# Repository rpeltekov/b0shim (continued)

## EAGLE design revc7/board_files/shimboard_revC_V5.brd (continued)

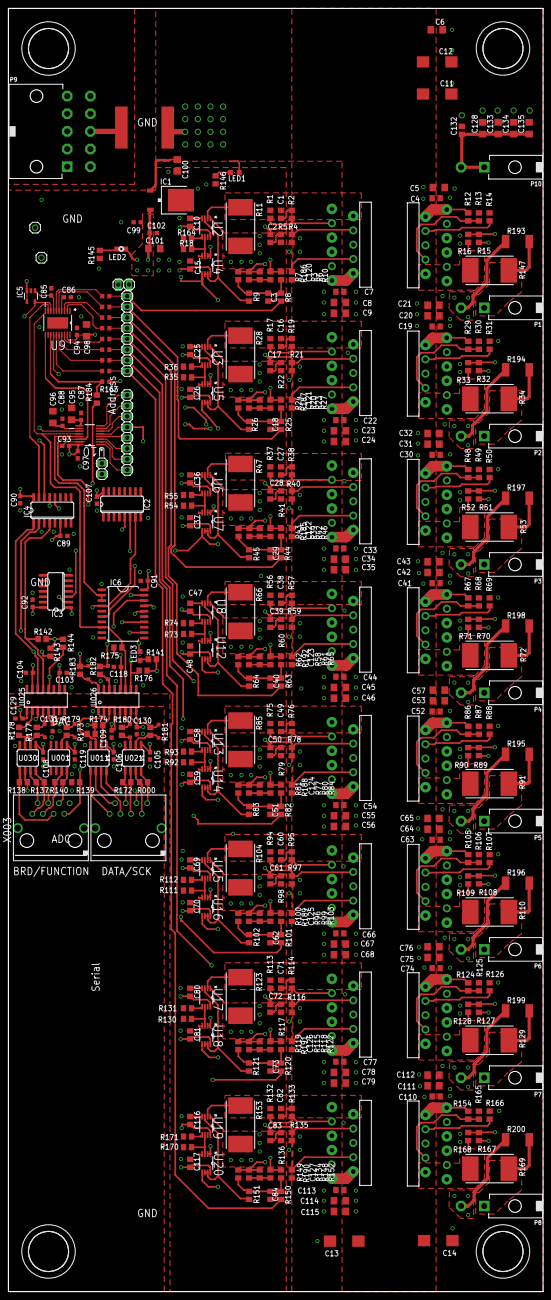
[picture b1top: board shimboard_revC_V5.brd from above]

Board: 4 copper layers, 127.0 x 304.8 mm, 411 parts (0 on the bottom side), 229 nets.

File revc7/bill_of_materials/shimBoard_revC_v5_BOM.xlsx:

Qty | Value | Device | Package | Manufacturer Part # | Parts | Description | MPN | SPICEPREFIX
SMT Components
3 |  | LEDCHIPLED_0805 | CHIPLED_0805 | LTST-C191KRKT | LED1, LED2, LED3 | LED
8 | 0 | R-US_R0603 | R0603 | ‎ERJ-3GEY0R00V‎ | R155, R156, R157, R158, R159, R160, R161, R162 | RESISTOR, | American symbol | R
24 | 0.1uF | C-USC0603 | C0603 | CC0603ZRY5V9BB104‎ | C85, C86, C87, C88, C89, C90, C91, C92, C93, C94, C99, C102, C103, C104, C105, 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 | CAPACITOR | American symbol | C
33 | 0.1uF | C-USC0805 | C0805 | CL21F104ZBCNNNC‎ | C4, C7, C10, C15, C19, C22, C25, C26, C30, C33, C36, C37, C41, C44, C47, C48, C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 | CAPACITOR | American symbol | C
16 | 0.2 | R-US_R4527 | R4527 | WSR5R2000FEA | R11, R28, R34, R47, R53, R66, R72, R85, R91, R104, R110, R123, R129, R147, R153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 | RESISTOR | American symbol | R
1 | 881070 | 881070 | 881 | ‎0881070.UR‎ | U031
7 | 100 | R-US_R0805 | R0805 | ‎ERA-6AEB101V‎ | R000, R137, R138, R139, R140, R172, R184 | RESISTOR | American symbol | 100
16 | 100pF | C-USC0805 | C0805 | 08051A101FAT2A‎ | C1, C2, C16, C17, C27, C28, C38, C39, C49, C50, C60, C61, C71, C72, C82, C83 | CAPACITOR | American symbol | C
4 | 100u | CPOL-USD/7343-31W | D/7343-31W | T491X107K025AT‎ | C11, C12, C13, C14 | POLARIZED CAPACITOR | American symbol | C
1 | 10k | R-US_R0603 | R0603 | RNCF0805DTE10K0‎ | R163 | RESISTOR | American symbol | R
48 | 10k | R-US_R0805 | R0805 | RNCF0805DTE10K0‎ | R8, R9, R10, R14, R18, R25, R26, R27, R31, R35, R36, R44, R45, R46, R50, R54, R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 | RESISTOR | American symbol | R
41 | 10uF | C-USC1206 | C1206 | CL31A106KAHNNNE‎ | C5, C6, C8, C9, C20, C21, C23, C24, C31, C32, C34, C35, C42, C43, C45, C46, C53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 | CAPACITOR | American symbol | C
7 | 1N4148 | 1N4148 | 1N4148 | 1N4148W-7-F | U040, U041, U042, U043, U044, U045, U046
1 | 1n | C-USC0805 | C0805 | C0805C102K1RACTU‎ | C3 | CAPACITOR | American symbol | 1n
7 | 1n | C-USC0805 | C0805 | C0805C102K1RACTU‎ | C18, C29, C40, C51, C62, C73, C84 | CAPACITOR | American symbol | C
1 | 1uF | C-USC0603 | C0603 | CL10A105KA8NNNC‎ | C97 | CAPACITOR | American symbol | C
8 | 220p | C-USC0805 | C0805 | C0805C221M5RACTU‎ | C120, C121, C122, C123, C124, C125, C126, C127 | CAPACITOR | American symbol | C
8 | 22k | R-US_R0805 | R0805 | KTR10EZPF2202‎ | R3, R20, R39, R58, R77, R96, R115, R134 | RESISTOR | American symbol | R
8 | 2M | R-US_R0805 | R0805 | CPF0805B2M0E1‎ | R185, R186, R187, R188, R189, R190, R191, R192 | RESISTOR | American symbol | R
35 | 2k | R-US_R0805 | R0805 | ERA-6AEB202V‎ | R13, R15, R16, R30, R32, R33, R49, R51, R52, R68, R70, R71, R87, R89, R90, R106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 | RESISTOR | American symbol | R
14 | 330 | R-US_R0805 | R0805 | ESR10EZPF3300‎ | R142, R143, R144, R173, R174, R175, R176, R177, R178, R179, R180, R181, R182, R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 | RESISTOR | American symbol | 330
8 | 330 | R-US_R2512 | R2512 | RHC2512FT330R | R193, R194, R195, R196, R197, R198, R199, R200 | RESISTOR | American symbol
16 | 5.1k | R-US_R0805 | R0805 | ESR10EZPF5101‎ | R2, R19, R38, R57, R76, R95, R114, R133, R5, R22, R41, R60, R79, R98, R117, R136 | RESISTOR | American symbol | R
16 | 51.1k | R-US_R0805 | R0805 | ERA-6AEB5112V‎ | R1, R4, R17, R21, R37, R40, R56, R59, R75, R78, R94, R97, R113, R116, R132, R135 | RESISTOR | American symbol | R
16 | 68.1k | R-US_R0805 | R0805 | ERA-6AEB6812V‎ | R6, R7, R23, R24, R42, R43, R61, R62, R80, R81, R99, R100, R118, R119, R148, R1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 | RESISTOR | American symbol | R
1 | 7400D | 7400D | SO14 | 74HCT00D,653‎ | IC3 | Quad 2-input NAND gate
1 | 74HCT138D | 74LS138D | SO16 | 74HCT138D,653 | IC4 | 3-line to 8-line DECODER/DEMULTIPLEXER
1 | 74HCT240DW | 74LS240DW | SO20W | SN74HCT240DW‎ | IC6 | Octal BUFFER and LINE DRIVER, 3-state
1 | 74LS279D | 74LS279D | SO16 | SN74LS279ADR‎ | IC2 | Quadruple S-R LATCH
1 | ACSL-6400 | ACSL-6400 | ACSL-SO16 | ACSL-6400-50TE | U025 | Quad-Channel All-in-One Optocoupler
1 | ACSL-6420 | ACSL-6420 | ACSL-SO16 | ACSL-6420-00TE | U026 | Quad-Channel Bi-Directional Optocoupler
3 | 65LVDS34 | 65LVDS34 | SO08-1 | SN65LVDS34DR‎ | U001, U021, U030
1 | 65LVDS9638 | 65LVDS9638 | SO08-1 | SN65LVDS9638D‎ | U011
8 | INA170EA/250 | INA170EA/250 | SOP65P490X110-8N | INA170EA/250 | U2, U3, U6, U8, U13, U15, U17, U19 | Bidirectional CURRENT SHUNT MONITOR | INA170EA/250
1 | LINEAR_7805DT | LINEAR_7805DT | LINEAR_TO252 | L7805CDT-TR | IC1 | Positive VOLTAGE REGULATOR
1 | LMV321M5 | LMV321M5 | SOT23-5 | LMV321M5/NOPB‎ | IC5 | General Purpose, Low Voltage, Rail-to-Rail Output Operational Amplifiers
1 | LTC1863CGNPBF | LTC1863CGNPBF | SOP63P600X175-16N | LTC1863CGN#PBF | U10 | ADC | LTC1863CGN#PBF
1 | LTC2656BCFE-L16PBF | LTC2656BCFE-L16PBF | SOP65P640X120-21N | LTC2656BCFE-L16#PBF | U9 | Octal DACs with 10ppm/掳C Max Reference | LTC2656BCFE-H16#PBF
8 | OPA2340EA/250 | OPA2340EA/250 | SOP65P490X110-8N | OPA2340EA/250 | U4, U5, U7, U12, U14, U16, U18, U20 | OPERATIONAL AMPLIFIERS | OPA2340EA/250
Throughole Components
1 | RJ45V-Shielded | RJ45V | RJ45-Vertical | RJE061881120 | X002
1 | RJ45V-Shielded | RJ45V | RJ45-Vertical | RJE081880110 | X003
16 | OPA549 | OPA549 | OPA549 | OPA549T | U$1, U$2, U$3, U$4, U$5, U$6, U$7, U$8, U$9, U$10, U$11, U$12, U$13, U$14, U$15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
9 | Molex Mini-Fit Jr. Right Angle Header (2 pos) | Molex Mini-Fit Jr. Right Angle Header (2 pos) | Molex Mini-Fit Jr. Right Angle Header (2 pos) | MOLEX 0026013114 | P1, P2, P3, P4, P5, P6, P7, P8, P10
1 | Molex Mini-Fit Jr. Right Angle Header (10 pos) | Molex Mini-Fit Jr. Right Angle Header (10 pos) | Molex Mini-Fit Jr. Right Angle Header (10 pos) | MOLEX 0039300100 | P9

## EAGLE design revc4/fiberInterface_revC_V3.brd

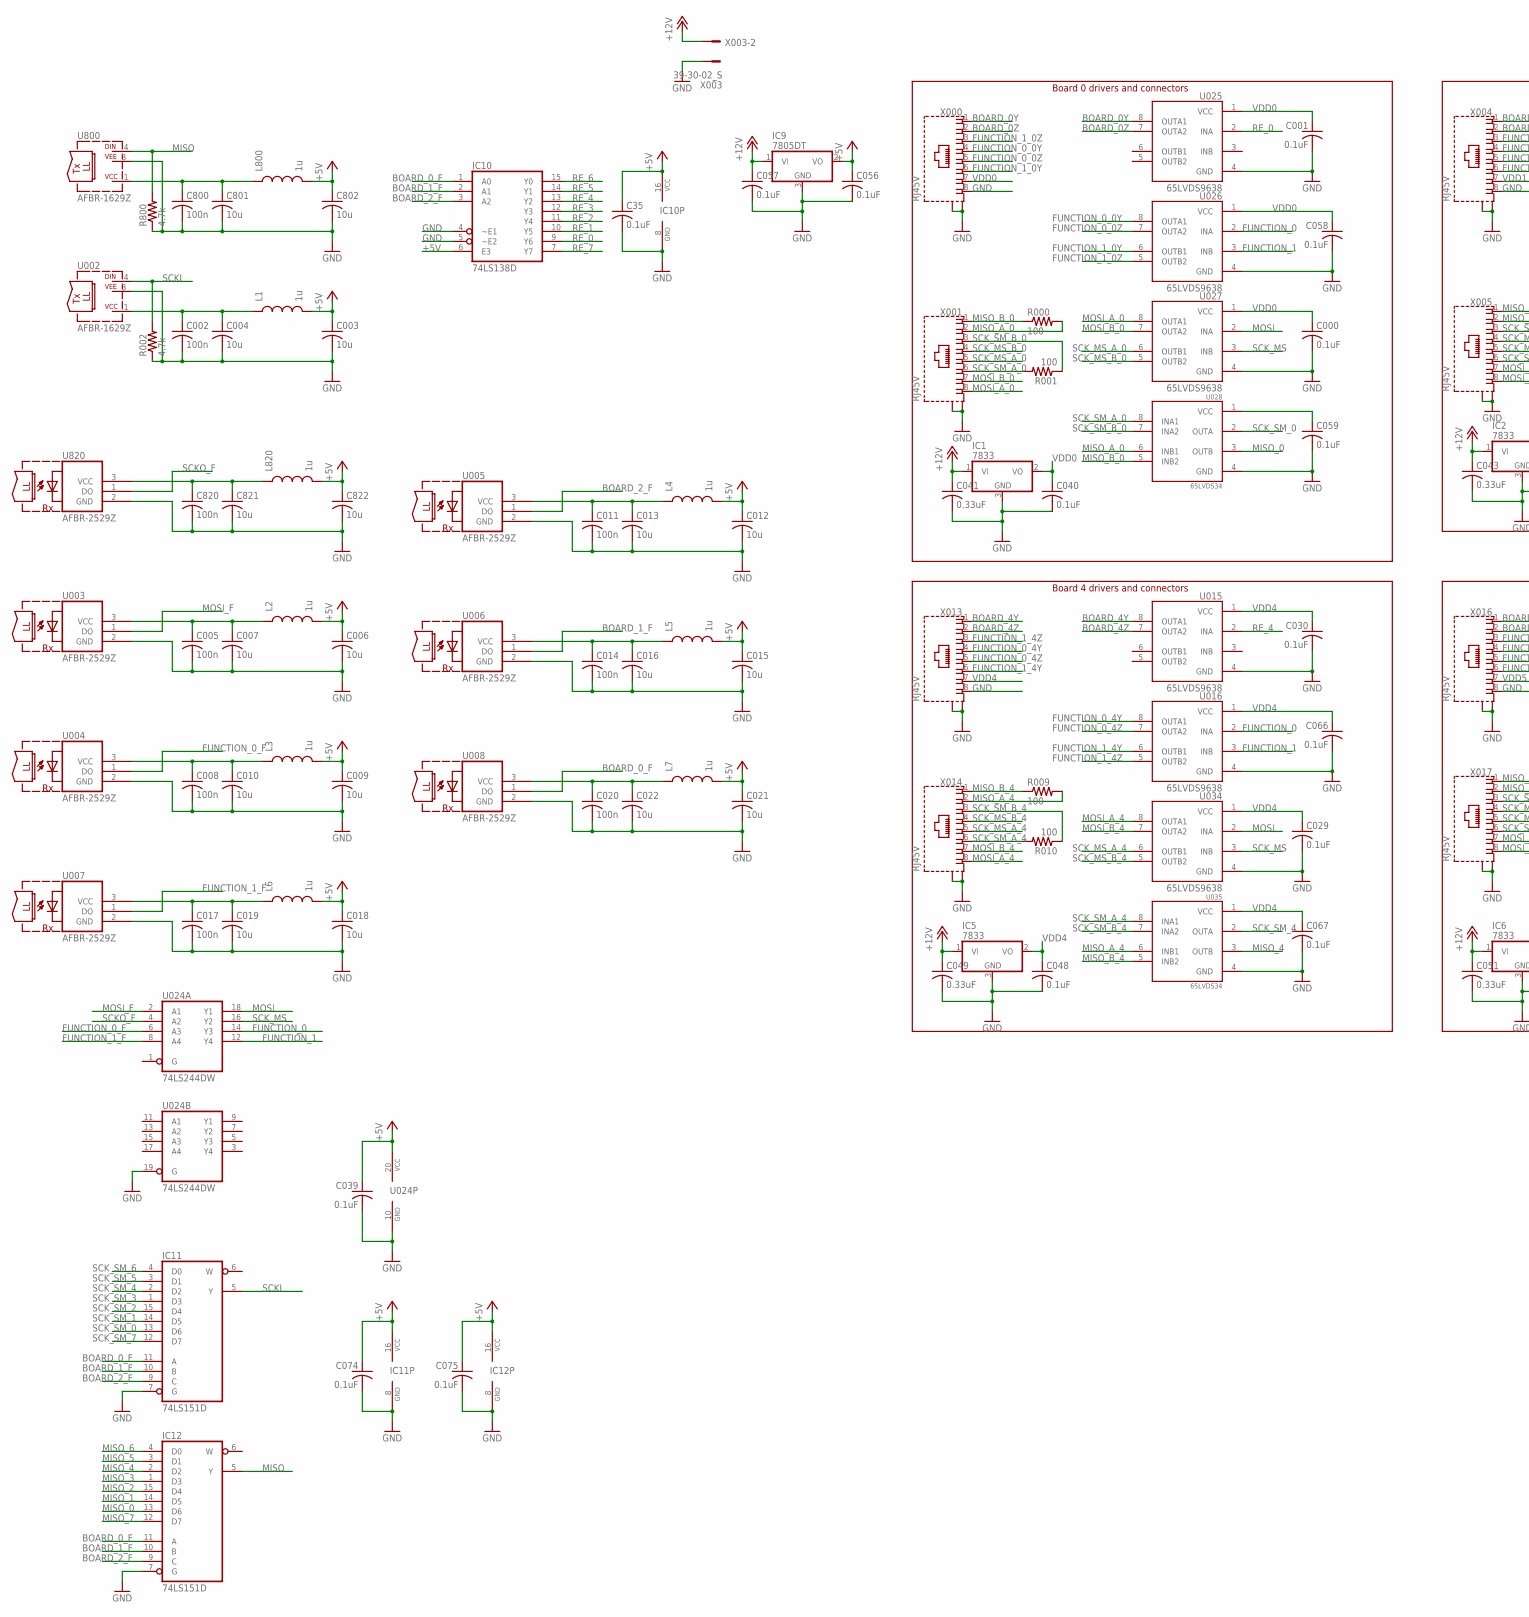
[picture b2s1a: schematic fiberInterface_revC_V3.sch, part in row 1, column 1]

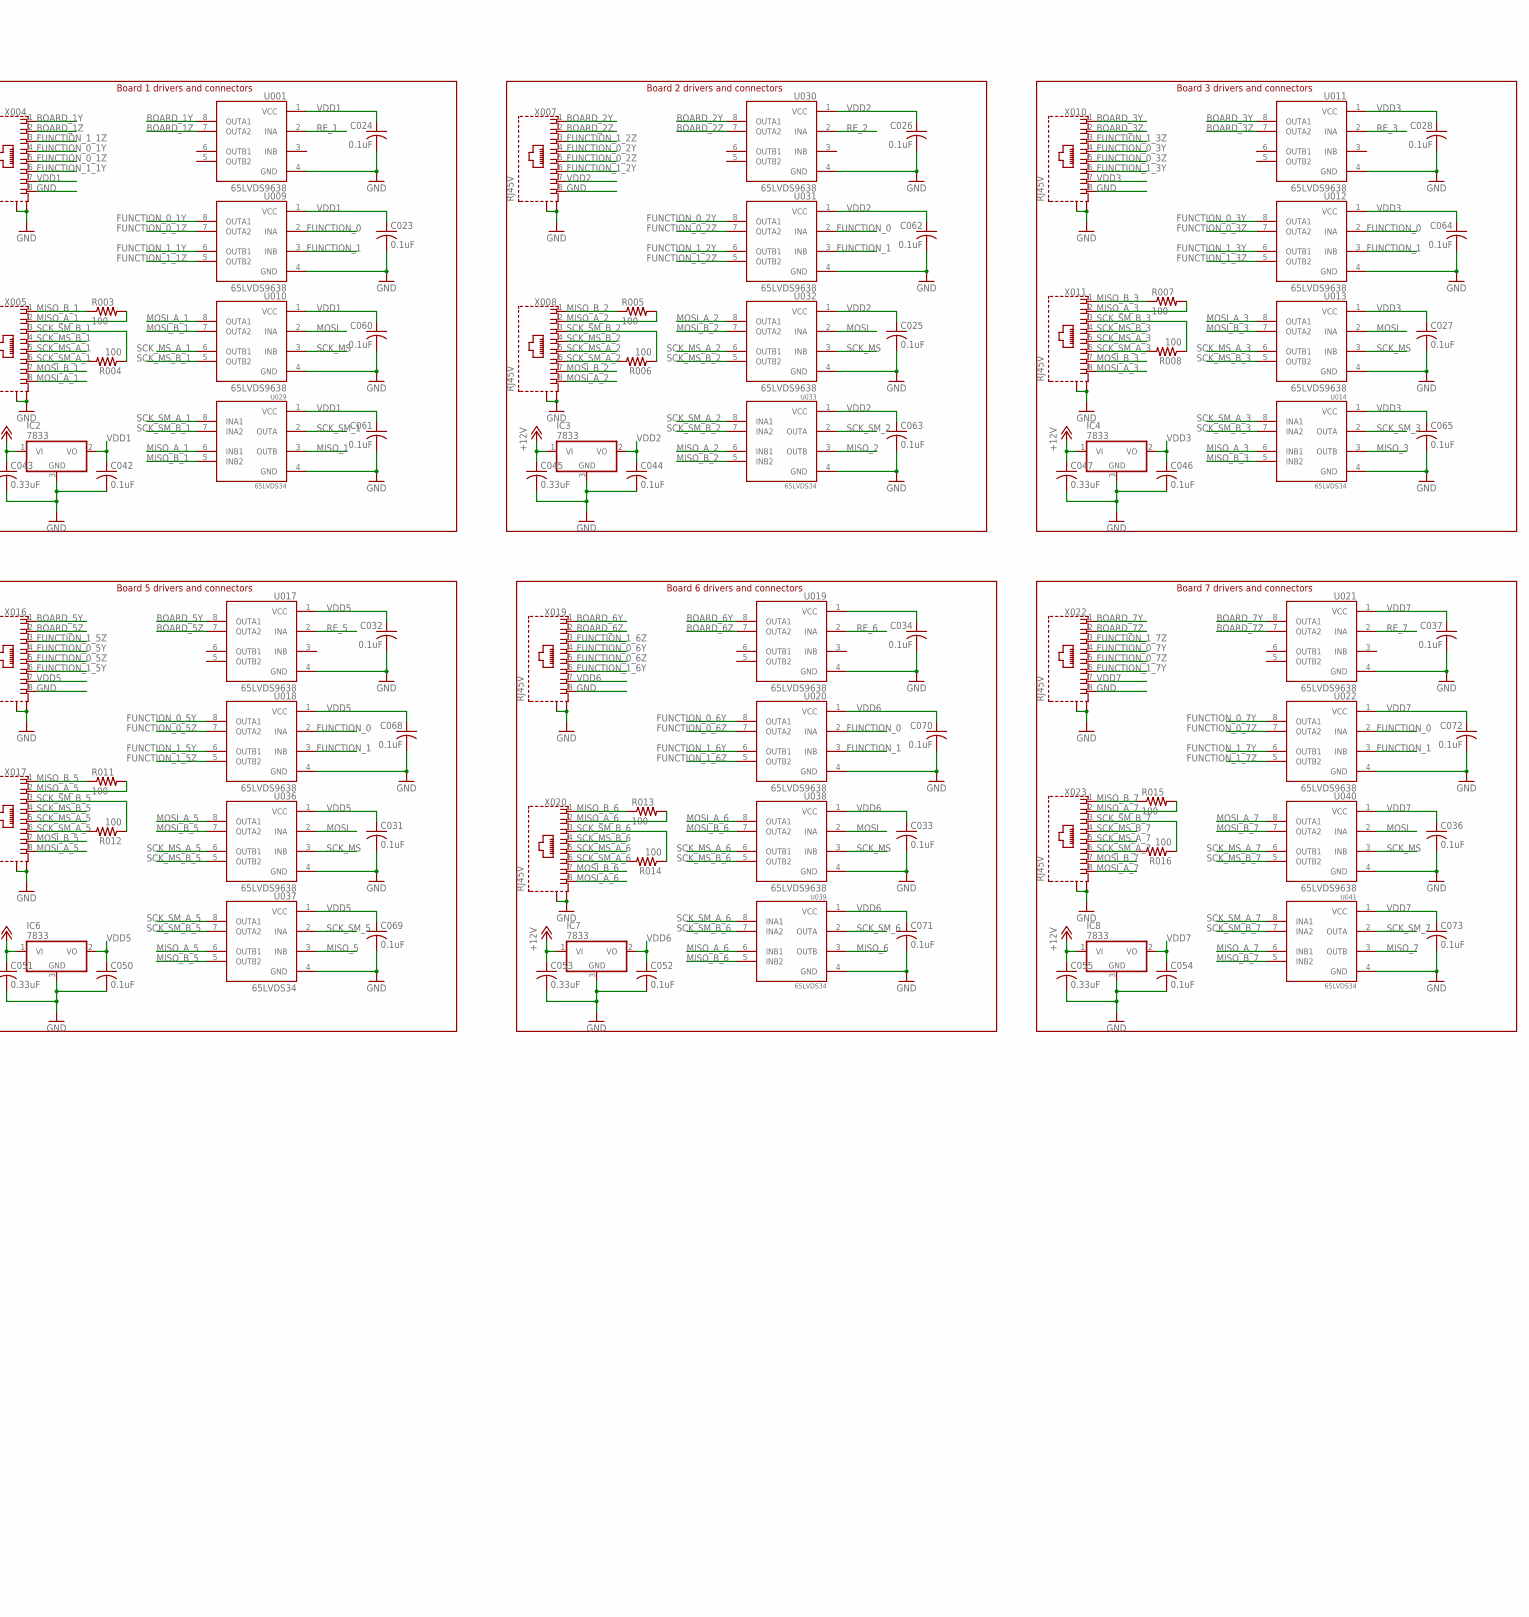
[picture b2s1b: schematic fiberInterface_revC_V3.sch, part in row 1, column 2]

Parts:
C000, C001, C023, C024, C025, C026, C027, C028, C029, C030, C031, C032, C033, C034, C35, C036, C037, C039, C056, C057, C058, C059, C060, C061, C062, C063, C064, C065, C066, C067, C068, C069, C070, C071, C072, C073, C074, C075: 0.1uF; C0603
C002, C005, C008, C011, C014, C017, C020, C800, C820: 100n; C0805
C003, C004, C006, C007, C009, C010, C012, C013, C015, C016, C018, C019, C021, C022, C801, C802, C821, C822: 10u; C1206
C040, C042, C044, C046, C048, C050, C052, C054: 0.1uF; C0805
C041, C043, C045, C047, C049, C051, C053, C055: 0.33uF; C0805
IC1, IC2, IC3, IC4, IC5, IC6, IC7, IC8: 7833; TO252
IC9: 7805DT; TO252
IC10: 74LS138D; SO16
IC11, IC12: 74LS151D; SO16
L1, L2, L3, L4, L5, L6, L7, L800, L820: 1u; 0805
R000, R001, R003, R004, R005, R006, R007, R008, R009, R010, R011, R012, R013, R014, R015, R016: 100; R0805
R002, R800: 4.7k; R0805
U001, U009, U010, U011, U012, U013, U015, U016, U017, U018, U019, U020, U021, U022, U025, U026, U027, U030, U031, U032, U034, U036, U038, U040: 65LVDS9638; SO08-1
U002, U800: AFBR-1629Z; HFBR-15X3
U003, U004, U005, U006, U007, U008, U820: AFBR-2529Z; HFBR-15X3
U014, U028, U029, U033, U035, U037, U039, U041: 65LVDS34; SO08-1
U024: 74LS244DW; SO20W
X000, X001, X004, X005, X007, X008, X010, X011, X013, X014, X016, X017, X019, X020, X022, X023: RJ45V; RJ45-VERTICAL
X003: 39-30-02_S; 39-30-?02?

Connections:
+5V: C003.1, C006.1, C009.1, C012.1, C015.1, C018.1, C021.1, C35.1, C039.1, C056.1, C074.1, C075.1, C802.1, C822.1, IC9.2 (VO), IC10.6 (E3), IC10.16 (VCC), IC11.16 (VCC), IC12.16 (VCC), L1.2, L2.2, L3.2, L4.2, L5.2, L6.2, L7.2, L800.2, L820.2, U024.20 (VCC)
+12V: C041.1, C043.1, C045.1, C047.1, C049.1, C051.1, C053.1, C055.1, C057.1, IC1.1 (VI), IC2.1 (VI), IC3.1 (VI), IC4.1 (VI), IC5.1 (VI), IC6.1 (VI), IC7.1 (VI), IC8.1 (VI), IC9.1 (VI), X003.2
BOARD_0Y: U025.8 (OUTA1), X000.1
BOARD_0Z: U025.7 (OUTA2), X000.2
BOARD_0_F: IC10.1 (A0), IC11.11 (A), IC12.11 (A), U008.1 (DO)
BOARD_1Y: U001.8 (OUTA1), X004.1
BOARD_1Z: U001.7 (OUTA2), X004.2
BOARD_1_F: IC10.2 (A1), IC11.10 (B), IC12.10 (B), U006.1 (DO)
BOARD_2Y: U030.8 (OUTA1), X007.1
BOARD_2Z: U030.7 (OUTA2), X007.2
BOARD_2_F: IC10.3 (A2), IC11.9 (C), IC12.9 (C), U005.1 (DO)
BOARD_3Y: U011.8 (OUTA1), X010.1
BOARD_3Z: U011.7 (OUTA2), X010.2
BOARD_4Y: U015.8 (OUTA1), X013.1
BOARD_4Z: U015.7 (OUTA2), X013.2
BOARD_5Y: U017.8 (OUTA1), X016.1
BOARD_5Z: U017.7 (OUTA2), X016.2
BOARD_6Y: U019.8 (OUTA1), X019.1
BOARD_6Z: U019.7 (OUTA2), X019.2
BOARD_7Y: U021.8 (OUTA1), X022.1
BOARD_7Z: U021.7 (OUTA2), X022.2
FUNCTION_0: U009.2 (INA), U012.2 (INA), U016.2 (INA), U018.2 (INA), U020.2 (INA), U022.2 (INA), U024.14 (Y3), U026.2 (INA), U031.2 (INA)
FUNCTION_0_0Y: U026.8 (OUTA1), X000.4
FUNCTION_0_0Z: U026.7 (OUTA2), X000.5
FUNCTION_0_1Y: U009.8 (OUTA1), X004.4
FUNCTION_0_1Z: U009.7 (OUTA2), X004.5
FUNCTION_0_2Y: U031.8 (OUTA1), X007.4
FUNCTION_0_2Z: U031.7 (OUTA2), X007.5
FUNCTION_0_3Y: U012.8 (OUTA1), X010.4
FUNCTION_0_3Z: U012.7 (OUTA2), X010.5
FUNCTION_0_4Y: U016.8 (OUTA1), X013.4
FUNCTION_0_4Z: U016.7 (OUTA2), X013.5
FUNCTION_0_5Y: U018.8 (OUTA1), X016.4
FUNCTION_0_5Z: U018.7 (OUTA2), X016.5
FUNCTION_0_6Y: U020.8 (OUTA1), X019.4
FUNCTION_0_6Z: U020.7 (OUTA2), X019.5
FUNCTION_0_7Y: U022.8 (OUTA1), X022.4
FUNCTION_0_7Z: U022.7 (OUTA2), X022.5
FUNCTION_0_F: U004.1 (DO), U024.6 (A3)
FUNCTION_1: U009.3 (INB), U012.3 (INB), U016.3 (INB), U018.3 (INB), U020.3 (INB), U022.3 (INB), U024.12 (Y4), U026.3 (INB), U031.3 (INB)
FUNCTION_1_0Y: U026.6 (OUTB1), X000.6
FUNCTION_1_0Z: U026.5 (OUTB2), X000.3
FUNCTION_1_1Y: U009.6 (OUTB1), X004.6
FUNCTION_1_1Z: U009.5 (OUTB2), X004.3
FUNCTION_1_2Y: U031.6 (OUTB1), X007.6
FUNCTION_1_2Z: U031.5 (OUTB2), X007.3
FUNCTION_1_3Y: U012.6 (OUTB1), X010.6
FUNCTION_1_3Z: U012.5 (OUTB2), X010.3
FUNCTION_1_4Y: U016.6 (OUTB1), X013.6
FUNCTION_1_4Z: U016.5 (OUTB2), X013.3
FUNCTION_1_5Y: U018.6 (OUTB1), X016.6
FUNCTION_1_5Z: U018.5 (OUTB2), X016.3
FUNCTION_1_6Y: U020.6 (OUTB1), X019.6
FUNCTION_1_6Z: U020.5 (OUTB2), X019.3
FUNCTION_1_7Y: U022.6 (OUTB1), X022.6
FUNCTION_1_7Z: U022.5 (OUTB2), X022.3
FUNCTION_1_F: U007.1 (DO), U024.8 (A4)
GND: C000.2, C001.2, C002.2, C003.2, C004.2, C005.2, C006.2, C007.2, C008.2, C009.2, C010.2, C011.2, C012.2, C013.2, C014.2, C015.2, C016.2, C017.2, C018.2, C019.2, C020.2, C021.2, C022.2, C023.2, C024.2, C025.2, C026.2, C027.2, C028.2, C029.2, C030.2, C031.2, C032.2, C033.2, C034.2, C35.2, C036.2, C037.2, C039.2, C040.2, C041.2, C042.2, C043.2, C044.2, C045.2, C046.2, C047.2, C048.2, C049.2, C050.2, C051.2, C052.2, C053.2, C054.2, C055.2, C056.2, C057.2, C058.2, C059.2, C060.2, C061.2, C062.2, C063.2, C064.2, C065.2, C066.2, C067.2, C068.2, C069.2, C070.2, C071.2, C072.2, C073.2, C074.2, C075.2, C800.2, C801.2, C802.2, C820.2, C821.2, C822.2, IC1.3 (GND), IC2.3 (GND), IC3.3 (GND), IC4.3 (GND), IC5.3 (GND), IC6.3 (GND), IC7.3 (GND), IC8.3 (GND), IC9.3 (GND), IC10.4 (~E1), IC10.5 (~E2), IC10.8 (GND), IC11.7 (G), IC11.8 (GND), IC12.7 (G), IC12.8 (GND), R002.1, R800.1, U001.4 (GND), U002.3 (VEE), U003.2 (GND), U004.2 (GND), U005.2 (GND), U006.2 (GND), U007.2 (GND), U008.2 (GND), U009.4 (GND), U010.4 (GND), U011.4 (GND), U012.4 (GND), U013.4 (GND), U014.4 (GND), U015.4 (GND), U016.4 (GND), U017.4 (GND), U018.4 (GND), U019.4 (GND), U020.4 (GND), U021.4 (GND), U022.4 (GND), U024.10 (GND), U024.19 (G), U025.4 (GND), U026.4 (GND), U027.4 (GND), U028.4 (GND), U029.4 (GND), U030.4 (GND), U031.4 (GND), U032.4 (GND), U033.4 (GND), U034.4 (GND), U035.4 (GND), U036.4 (GND), U037.4 (GND), U038.4 (GND), U039.4 (GND), U040.4 (GND), U041.4 (GND), U800.3 (VEE), U820.2 (GND), X000.8, X000.G1 (S), X000.G2 (S), X001.G1 (S), X001.G2 (S), X003.1, X004.8, X004.G1 (S), X004.G2 (S), X005.G1 (S), X005.G2 (S), X007.8, X007.G1 (S), X007.G2 (S), X008.G1 (S), X008.G2 (S), X010.8, X010.G1 (S), X010.G2 (S), X011.G1 (S), X011.G2 (S), X013.8, X013.G1 (S), X013.G2 (S), X014.G1 (S), X014.G2 (S), X016.8, X016.G1 (S), X016.G2 (S), X017.G1 (S), X017.G2 (S), X019.8, X019.G1 (S), X019.G2 (S), X020.G1 (S), X020.G2 (S), X022.8, X022.G1 (S), X022.G2 (S), X023.G1 (S), X023.G2 (S)
MISO: IC12.5 (Y), R800.2, U800.4 (DIN)
MISO_0: IC12.13 (D6), U028.3 (OUTB)
MISO_1: IC12.14 (D5), U029.3 (OUTB)
MISO_2: IC12.15 (D4), U033.3 (OUTB)
MISO_3: IC12.1 (D3), U014.3 (OUTB)
MISO_4: IC12.2 (D2), U035.3 (OUTB)
MISO_5: IC12.3 (D1), U037.3 (INB)
MISO_6: IC12.4 (D0), U039.3 (OUTB)
MISO_7: IC12.12 (D7), U041.3 (OUTB)
MISO_A_0: R000.2, U028.6 (INB1), X001.2
MISO_A_1: R003.2, U029.6 (INB1), X005.2
MISO_A_2: R005.2, U033.6 (INB1), X008.2
MISO_A_3: R007.2, U014.6 (INB1), X011.2
MISO_A_4: R009.2, U035.6 (INB1), X014.2
MISO_A_5: R011.2, U037.6 (OUTB1), X017.2
MISO_A_6: R013.2, U039.6 (INB1), X020.2
MISO_A_7: R015.2, U041.6 (INB1), X023.2
MISO_B_0: R000.1, U028.5 (INB2), X001.1
MISO_B_1: R003.1, U029.5 (INB2), X005.1
MISO_B_2: R005.1, U033.5 (INB2), X008.1
MISO_B_3: R007.1, U014.5 (INB2), X011.1
MISO_B_4: R009.1, U035.5 (INB2), X014.1
MISO_B_5: R011.1, U037.5 (OUTB2), X017.1
MISO_B_6: R013.1, U039.5 (INB2), X020.1
MISO_B_7: R015.1, U041.5 (INB2), X023.1
MOSI: U010.2 (INA), U013.2 (INA), U024.18 (Y1), U027.2 (INA), U032.2 (INA), U034.2 (INA), U036.2 (INA), U038.2 (INA), U040.2 (INA)
MOSI_A_0: U027.8 (OUTA1), X001.8
MOSI_A_1: U010.8 (OUTA1), X005.8
MOSI_A_2: U032.8 (OUTA1), X008.8
MOSI_A_3: U013.8 (OUTA1), X011.8
MOSI_A_4: U034.8 (OUTA1), X014.8
MOSI_A_5: U036.8 (OUTA1), X017.8
MOSI_A_6: U038.8 (OUTA1), X020.8
MOSI_A_7: U040.8 (OUTA1), X023.8
MOSI_B_0: U027.7 (OUTA2), X001.7
MOSI_B_1: U010.7 (OUTA2), X005.7
MOSI_B_2: U032.7 (OUTA2), X008.7
MOSI_B_3: U013.7 (OUTA2), X011.7
MOSI_B_4: U034.7 (OUTA2), X014.7
MOSI_B_5: U036.7 (OUTA2), X017.7
MOSI_B_6: U038.7 (OUTA2), X020.7
MOSI_B_7: U040.7 (OUTA2), X023.7
MOSI_F: U003.1 (DO), U024.2 (A1)
unnamed: C800.1, C801.1, L800.1, U800.1 (VCC)
unnamed: C002.1, C004.1, L1.1, U002.1 (VCC)
unnamed: C005.1, C007.1, L2.1, U003.3 (VCC)
unnamed: C008.1, C010.1, L3.1, U004.3 (VCC)
unnamed: C820.1, C821.1, L820.1, U820.3 (VCC)
unnamed: C011.1, C013.1, L4.1, U005.3 (VCC)
unnamed: C014.1, C016.1, L5.1, U006.3 (VCC)
unnamed: C017.1, C019.1, L6.1, U007.3 (VCC)
unnamed: C020.1, C022.1, L7.1, U008.3 (VCC)
RE_0: IC10.9 (Y6), U025.2 (INA)
RE_1: IC10.10 (Y5), U001.2 (INA)
RE_2: IC10.11 (Y4), U030.2 (INA)
RE_3: IC10.12 (Y3), U011.2 (INA)
RE_4: IC10.13 (Y2), U015.2 (INA)
RE_5: IC10.14 (Y1), U017.2 (INA)
RE_6: IC10.15 (Y0), U019.2 (INA)
RE_7: IC10.7 (Y7), U021.2 (INA)
SCKI: IC11.5 (Y), R002.2, U002.4 (DIN)
SCKO_F: U024.4 (A2), U820.1 (DO)
SCK_MS: U010.3 (INB), U013.3 (INB), U024.16 (Y2), U027.3 (INB), U032.3 (INB), U034.3 (INB), U036.3 (INB), U038.3 (INB), U040.3 (INB)
SCK_MS_A_0: U027.6 (OUTB1), X001.5
SCK_MS_A_1: U010.6 (OUTB1), X005.5
SCK_MS_A_2: U032.6 (OUTB1), X008.5
SCK_MS_A_3: U013.6 (OUTB1), X011.5
SCK_MS_A_4: U034.6 (OUTB1), X014.5
SCK_MS_A_5: U036.6 (OUTB1), X017.5
SCK_MS_A_6: U038.6 (OUTB1), X020.5
SCK_MS_A_7: U040.6 (OUTB1), X023.5
SCK_MS_B_0: U027.5 (OUTB2), X001.4
SCK_MS_B_1: U010.5 (OUTB2), X005.4
SCK_MS_B_2: U032.5 (OUTB2), X008.4
SCK_MS_B_3: U013.5 (OUTB2), X011.4
SCK_MS_B_4: U034.5 (OUTB2), X014.4
SCK_MS_B_5: U036.5 (OUTB2), X017.4
SCK_MS_B_6: U038.5 (OUTB2), X020.4
SCK_MS_B_7: U040.5 (OUTB2), X023.4
SCK_SM_0: IC11.13 (D6), U028.2 (OUTA)
SCK_SM_1: IC11.14 (D5), U029.2 (OUTA)
SCK_SM_2: IC11.15 (D4), U033.2 (OUTA)
SCK_SM_3: IC11.1 (D3), U014.2 (OUTA)
SCK_SM_4: IC11.2 (D2), U035.2 (OUTA)
SCK_SM_5: IC11.3 (D1), U037.2 (INA)
SCK_SM_6: IC11.4 (D0), U039.2 (OUTA)
SCK_SM_7: IC11.12 (D7), U041.2 (OUTA)
SCK_SM_A_0: R001.2, U028.8 (INA1), X001.6
SCK_SM_A_1: R004.2, U029.8 (INA1), X005.6
SCK_SM_A_2: R006.2, U033.8 (INA1), X008.6
SCK_SM_A_3: R008.2, U014.8 (INA1), X011.6
SCK_SM_A_4: R010.2, U035.8 (INA1), X014.6
SCK_SM_A_5: R012.2, U037.8 (OUTA1), X017.6
SCK_SM_A_6: R014.2, U039.8 (INA1), X020.6
SCK_SM_A_7: R016.2, U041.8 (INA1), X023.6
SCK_SM_B_0: R001.1, U028.7 (INA2), X001.3
SCK_SM_B_1: R004.1, U029.7 (INA2), X005.3
SCK_SM_B_2: R006.1, U033.7 (INA2), X008.3
SCK_SM_B_3: R008.1, U014.7 (INA2), X011.3
SCK_SM_B_4: R010.1, U035.7 (INA2), X014.3
SCK_SM_B_5: R012.1, U037.7 (OUTA2), X017.3
SCK_SM_B_6: R014.1, U039.7 (INA2), X020.3
SCK_SM_B_7: R016.1, U041.7 (INA2), X023.3
VDD0: C000.1, C001.1, C040.1, C058.1, C059.1, IC1.2 (VO), U025.1 (VCC), U026.1 (VCC), U027.1 (VCC), U028.1 (VCC), X000.7
VDD1: C023.1, C024.1, C042.1, C060.1, C061.1, IC2.2 (VO), U001.1 (VCC), U009.1 (VCC), U010.1 (VCC), U029.1 (VCC), X004.7
VDD2: C025.1, C026.1, C044.1, C062.1, C063.1, IC3.2 (VO), U030.1 (VCC), U031.1 (VCC), U032.1 (VCC), U033.1 (VCC), X007.7
VDD3: C027.1, C028.1, C046.1, C064.1, C065.1, IC4.2 (VO), U011.1 (VCC), U012.1 (VCC), U013.1 (VCC), U014.1 (VCC), X010.7
VDD4: C029.1, C030.1, C048.1, C066.1, C067.1, IC5.2 (VO), U015.1 (VCC), U016.1 (VCC), U034.1 (VCC), U035.1 (VCC), X013.7
VDD5: C031.1, C032.1, C050.1, C068.1, C069.1, IC6.2 (VO), U017.1 (VCC), U018.1 (VCC), U036.1 (VCC), U037.1 (VCC), X016.7
VDD6: C033.1, C034.1, C052.1, C070.1, C071.1, IC7.2 (VO), U019.1 (VCC), U020.1 (VCC), U038.1 (VCC), U039.1 (VCC), X019.7
VDD7: C036.1, C037.1, C054.1, C072.1, C073.1, IC8.2 (VO), U021.1 (VCC), U022.1 (VCC), U040.1 (VCC), U041.1 (VCC), X022.7

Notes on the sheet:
Board 0 drivers and connectors
Board 1 drivers and connectors
Board 2 drivers and connectors
Board 3 drivers and connectors
Board 4 drivers and connectors
Board 5 drivers and connectors
Board 6 drivers and connectors
Board 7 drivers and connectors

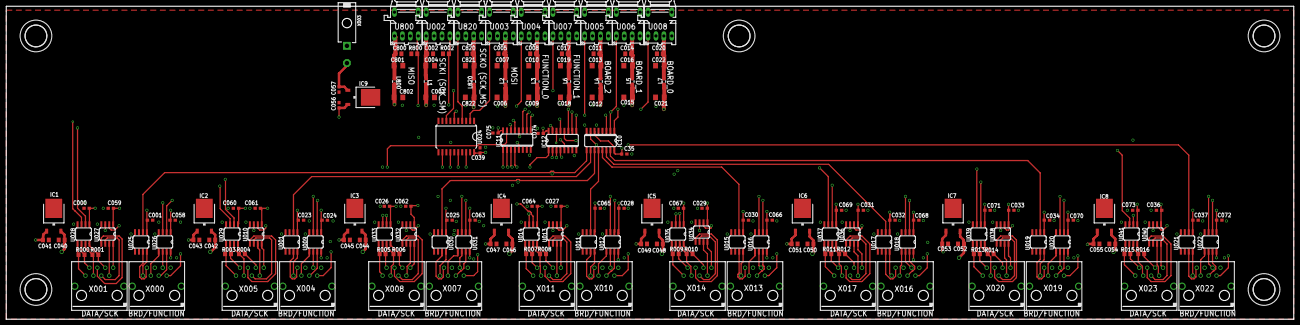
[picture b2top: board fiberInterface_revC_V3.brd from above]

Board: 4 copper layers, 412.7 x 100.3 mm, 179 parts (0 on the bottom side), 169 nets.

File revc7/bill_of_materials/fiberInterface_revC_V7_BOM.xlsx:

Qty | Value | Device | Package | Manufacturer Part # | Parts | Description | SPICEPREFIX
SMT Components
1 | LEDCHIP-LED0805 | CHIP-LED0805 | LED1 | LTST-C191KRKT | LED
38 | 0.1uF | C-USC0603 | C0603 | CC0603ZRY5V9BB104‎ | C000, C001, C023, C024, C025, C026, C027, C028, C029, C030, C031, C032, C033, C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 | CAPACITOR, American symbol | C
17 | 0.1uF | C-USC0805 | C0805 | CL21F104ZBCNNNC‎ | C040, C042, C044, C046, C048, C050, C052, C054, C002, C005, C008, C011, C014, C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 | CAPACITOR, American symbol | C
8 | 0.33uF | C-USC0805 | C0805 | CGA4J2X7R1H334K125AA | C041, C043, C045, C047, C049, C051, C053, C055 | CAPACITOR, American symbol | C
16 | 100 | R-US_R0805 | R0805 | ‎ERA-6AEB101V‎ | R000, R001, R003, R004, R005, R006, R007, R008, R009, R010, R011, R012, R013, R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 | RESISTOR, American symbol | R
18 | 10u | C-USC1206 | C1206 | CL31A106KAHNNNE‎ | C003, C004, C006, C007, C009, C010, C012, C013, C015, C016, C018, C019, C021, C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 | CAPACITOR, American symbol | C
9 | 1u | INDUCTOR0805 | 805 | GLFR1608T1R0M-LR | L1, L2, L3, L4, L5, L6, L7, L800, L820 | Inductors
3 | 4.7k | R-US_R0805 | R0805 | ERA-6AEB472V | R002, R017, R800 | RESISTOR, American symbol | R
8 | 65LVDS34 | 65LVDS34 | SO08-1 | SN65LVDS34DR‎ | U014, U028, U029, U033, U035, U039, U041
24 | 65LVDS9638 | 65LVDS9638 | SO08-1 | SN65LVDS9638D‎ | U001, U009, U010, U011, U012, U013, U015, U016, U017, U018, U019, U020, U021, U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
1 | 74HCT138D | 74HCT138D | SO16 | 74HCT138D,653 | IC10 | 3-line to 8-line DECODER/DEMULTIPLEXER
2 | 74HCT141 | CD74HCT151M | SO16 | CD74HCT151M | IC13, IC14 | Data SELECTOR/MULTIPLEXER
1 | 74HCT244DW | 74HCT244DW | SO20W | SN74HCT244DWR | U024 | Octal BUFFER and LINE DRIVER, 3-state
1 | LINEAR_7805DT | LINEAR_7805DT | TO252 | L7805CDT-TR | IC9 | Positive VOLTAGE REGULATOR
8 | 78M33 | 78M33 | TO252 | UA78M33CKVURG3 | IC1, IC2, IC3, IC4, IC5, IC6, IC7, IC8 | Positive VOLTAGE REGULATOR
1 | APD240 |  | SOD-123 | 1655-2311-1-ND | U050 | General purpose diode (2A current rating); replaced obsolete part
Throughole Components
2 | AFBR-1629Z | AFBR-16XXZ | HFBR-15X3 | AFBR-1629Z | U002, U800
7 | AFBR-2529Z | AFBR-26X4Z | HFBR-15X3 | AFBR-2529Z | U003, U004, U005, U006, U007, U008, U820
8 | RJ45V-Shielded | RJ45V | RJ45-Vertical | RJE061881120 | X001, X005, X008, X011, X014, X017, X020, X023
8 | RJ45V-Unshielded | RJ45V | RJ45-Vertical | RJE081880110 | X000, X004, X007, X010, X013, X016, X019, X022

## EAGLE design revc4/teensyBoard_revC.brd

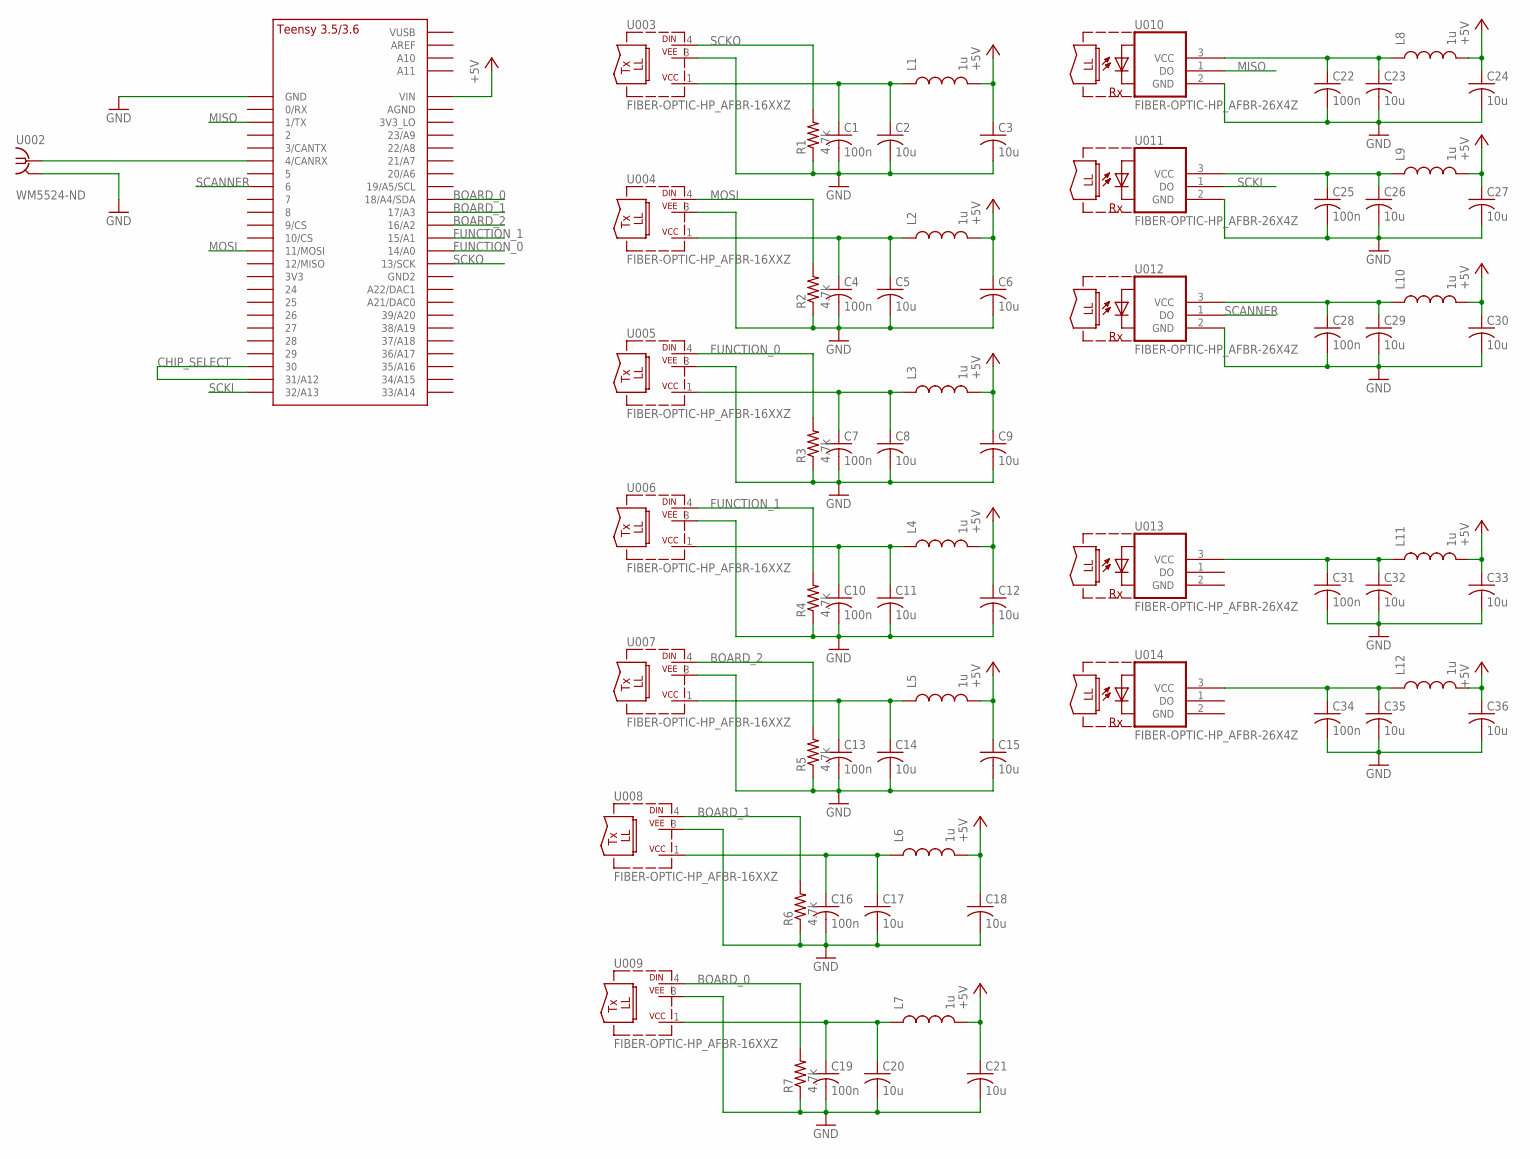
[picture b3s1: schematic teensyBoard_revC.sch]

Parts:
C1, C4, C7, C10, C13, C16, C19, C22, C25, C28, C31, C34: 100n; C0805
C2, C3, C5, C6, C8, C9, C11, C12, C14, C15, C17, C18, C20, C21, C23, C24, C26, C27, C29, C30, C32, C33, C35, C36: 10u; C1206
L1, L2, L3, L4, L5, L6, L7, L8, L9, L10, L11, L12: 1u; 0805
R1, R2, R3, R4, R5, R6, R7: 4.7k; M1206
U001: TEENSY_3.5/3.6_BASIC
U002: WM5524-ND
U003, U004, U005, U006, U007, U008, U009: FIBER-OPTIC-HP_AFBR-16XXZ; FIBER-OPTIC-HP_HFBR-15X3
U010, U011, U012, U013, U014: FIBER-OPTIC-HP_AFBR-26X4Z; FIBER-OPTIC-HP_HFBR-15X3

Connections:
+5V: C3.1, C6.1, C9.1, C12.1, C15.1, C18.1, C21.1, C24.1, C27.1, C30.1, C33.1, C36.1, L1.2, L2.2, L3.2, L4.2, L5.2, L6.2, L7.2, L8.2, L9.2, L10.2, L11.2, L12.2, U001.VIN
BOARD_0: R7.2, U001.18/A4/SDA, U009.4 (DIN)
BOARD_1: R6.2, U001.17/A3, U008.4 (DIN)
BOARD_2: R5.2, U001.16/A2, U007.4 (DIN)
CHIP_SELECT: U001.30, U001.31/A12
FUNCTION_0: R3.2, U001.14/A0, U005.4 (DIN)
FUNCTION_1: R4.2, U001.15/A1, U006.4 (DIN)
GND: C1.2, C2.2, C3.2, C4.2, C5.2, C6.2, C7.2, C8.2, C9.2, C10.2, C11.2, C12.2, C13.2, C14.2, C15.2, C16.2, C17.2, C18.2, C19.2, C20.2, C21.2, C22.2, C23.2, C24.2, C25.2, C26.2, C27.2, C28.2, C29.2, C30.2, C31.2, C32.2, C33.2, C34.2, C35.2, C36.2, R1.1, R2.1, R3.1, R4.1, R5.1, R6.1, R7.1, U001.GND, U002.2 (GND), U002.3 (GND), U003.3 (VEE), U004.3 (VEE), U005.3 (VEE), U006.3 (VEE), U007.3 (VEE), U008.3 (VEE), U009.3 (VEE), U010.2 (GND), U011.2 (GND), U012.2 (GND), U013.2 (GND), U014.2 (GND)
MISO: U001.1/TX, U010.1 (DO)
MOSI: R2.2, U001.11/MOSI, U004.4 (DIN)
unnamed: C22.1, C23.1, L8.1, U010.3 (VCC)
unnamed: C25.1, C26.1, L9.1, U011.3 (VCC)
unnamed: U001.4/CANRX, U002.1
unnamed: C1.1, C2.1, L1.1, U003.1 (VCC)
unnamed: C31.1, C32.1, L11.1, U013.3 (VCC)
unnamed: C34.1, C35.1, L12.1, U014.3 (VCC)
unnamed: C4.1, C5.1, L2.1, U004.1 (VCC)
unnamed: C7.1, C8.1, L3.1, U005.1 (VCC)
unnamed: C10.1, C11.1, L4.1, U006.1 (VCC)
unnamed: C13.1, C14.1, L5.1, U007.1 (VCC)
unnamed: C16.1, C17.1, L6.1, U008.1 (VCC)
unnamed: C19.1, C20.1, L7.1, U009.1 (VCC)
unnamed: C28.1, C29.1, L10.1, U012.3 (VCC)
SCANNER: U001.6, U012.1 (DO)
SCKI: U001.32/A13, U011.1 (DO)
SCKO: R1.2, U001.13/SCK, U003.4 (DIN)

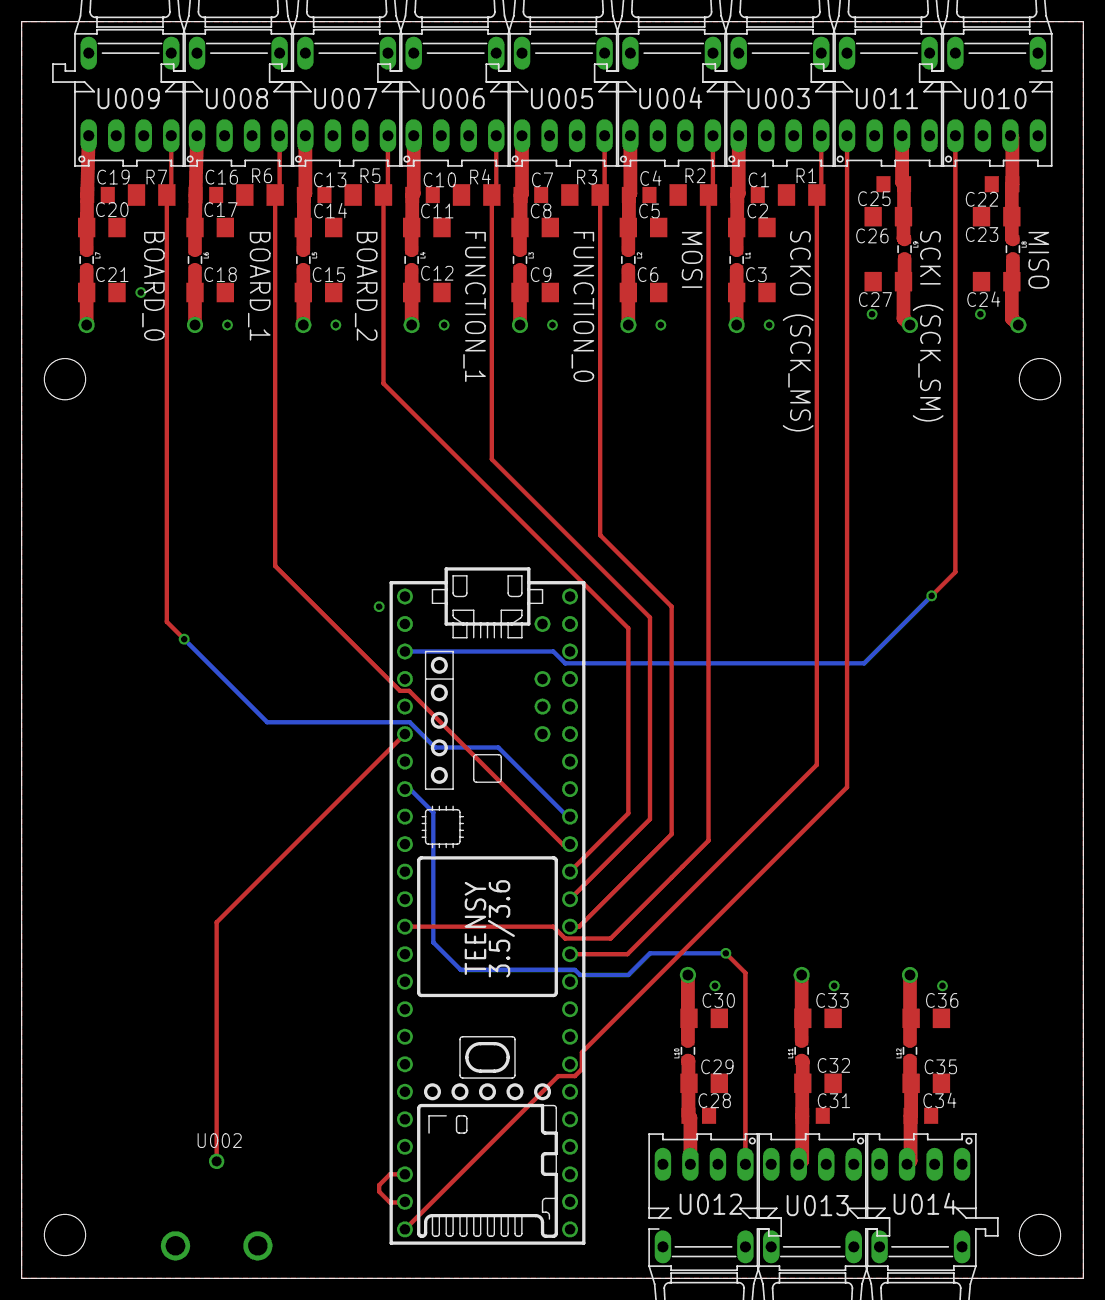
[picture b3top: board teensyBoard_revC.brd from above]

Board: 2 copper layers, 98.0 x 116.0 mm, 69 parts (0 on the bottom side), 26 nets.

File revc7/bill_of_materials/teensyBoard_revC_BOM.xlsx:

Qty | Value | Device | Package | Manufacturer Part # | Parts | Description
SMT Components
12 | 0.1u | C-USC0805 | C0805 | CC0603ZRY5V9BB104‎ | C1, C4, C7, C10, C13, C16, C19, C22, C25, C28, C31, C34 | CAPACITOR, American symbol
24 | 10u | C-USC1206 | C1206 | CL31A106KAHNNNE‎ | C2, C3, C5, C6, C8, C9, C11, C12, C14, C15, C17, C18, C20, C21, C23, C24, C26, 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 | CAPACITOR, American symbol
12 | 1u | INDUCTOR0805 | 805 | GLFR1608T1R0M-LR | L1, L2, L3, L4, L5, L6, L7, L8, L9, L10, L11, L12 | Inductors
7 | 4.7k | R-US_M0805 | M0805 | ERA-6AEB472V | R1, R2, R3, R4, R5, R6, R7 | RESISTOR, American symbol
Throughole Components
7 | AFBR-1629Z | FIBER-OPTIC-HP_AFBR-16XXZ | FIBER-OPTIC-HP_HFBR-15X3 | AFBR-1629Z | U003, U004, U005, U006, U007, U008, U009
5 | AFBR-2529Z | FIBER-OPTIC-HP_AFBR-26X4Z | FIBER-OPTIC-HP_HFBR-15X3 | AFBR-2529Z | U010, U011, U012, U013, U014
1 | TEENSY_3.5 | TEENSY_3.5/3.6_BASIC | TEENSY_3.5/3.6_BASIC | ADAFRUIT 3267 | U001
1 | WM5524-ND | WM5524-ND | WM5524-ND | MOLEX 731000105 | U002

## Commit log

2023-10-02 TPairShim is the current project
2023-10-10 two channels seem to be working in TPairShim
2023-11-03 adding git ignore
2023-11-03 updating git ignore
2023-11-03 adding all the src code
2023-11-03 update git ignore
2023-11-03 update gitignore last time so i can commit everything else
2023-11-03 new gitignore and submodules for tools
2023-11-03 up to date with new folder structure
2023-11-03 Create LICENSE
2023-11-04 man i think i am almost there......
2023-11-06 update finally in a working state
2023-11-06 working
2023-11-06 updated the compute basis so i can correctly sim julians coils
2023-11-07 pipeline for getting off resonance maps from 2 te scans works now.mostly finished
2023-11-07 fix slight issues in computebasis and also starting the compute current
2023-11-08 updated the code. least squares is working correctly and the images look almost good enough.
2023-11-08 multithreadin to speed up coil computation
2023-11-08 temporary changes to just be able to quick gen slices of coil...
2023-11-10 update gitignore
2023-11-10 gitignore
2023-12-09 i think this is the latest working version of my code base
2023-12-09 updated the phase_from_comp to accomodate 4 tes in the images
2023-12-09 fix typo
2023-12-09 removing unecessary import
2023-12-09 added no crop feature
2023-12-09 update for newalpha change
2023-12-09 another bug
2023-12-09 fukk this is stupid
2023-12-09 unwrapping phase making sure
